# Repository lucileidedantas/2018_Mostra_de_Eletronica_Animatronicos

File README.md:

# 2018_Mostra_de_Eletronica_Animatronicos
Arquivos, esquemáticos, sketchs e algumas imagens e vídeos da Mostra de eletrônica de 2018 onde cada grupo desenvolveu um animal diferente. Todos os prototipos usaram como base a plataforma arduino.
Fotos e vídeos do evento podem ser vistas no link: https://photos.app.goo.gl/8ZrHkMYPwSaBPpQG6.
Alguns animais, feitos em mdf e cortados a laser, foram desenhados pelos proprios estudantes. Estes arquivos também estão nas pastas referentes ao projeto. 
Outros animais foram feito de material reciclavel e material de papelaria.

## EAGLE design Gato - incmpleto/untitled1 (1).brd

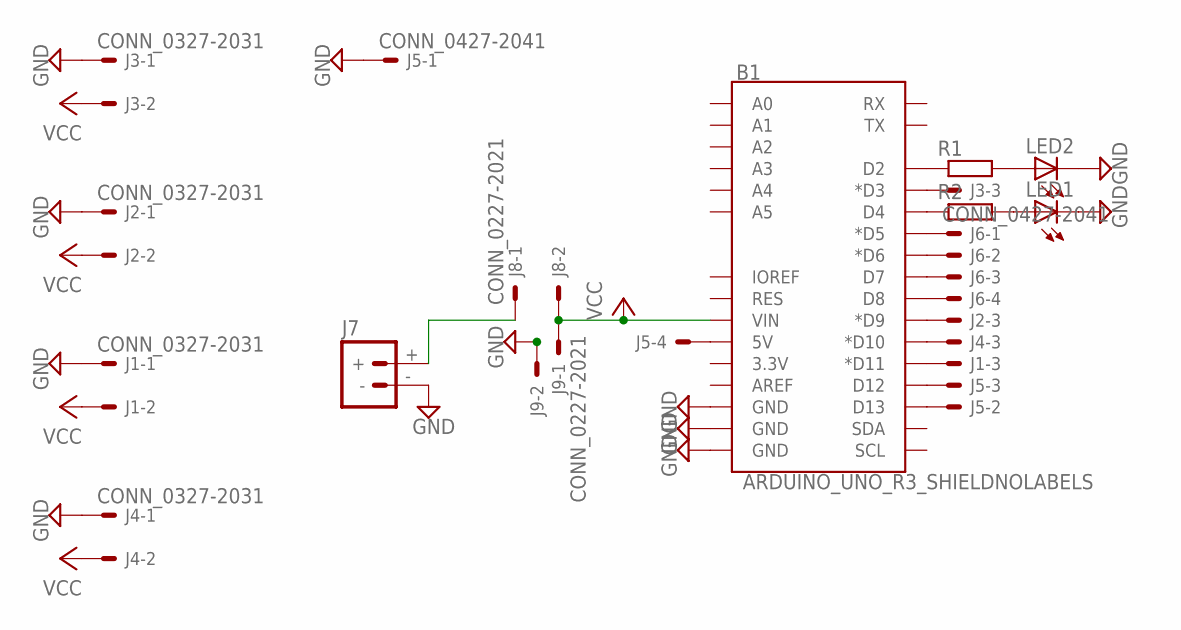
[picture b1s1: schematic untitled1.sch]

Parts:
B1: ARDUINO_UNO_R3_SHIELDNOLABELS; UNO_R3_SHIELD_NOLABELS
J1, J2, J3, J4: CONN_0327-2031; 6410-03
J5, J6: CONN_0427-2041; 6410-04
J7: BATTERY_CONNXT60; XT60
J8, J9: CONN_0227-2021; 6410-02
LED1, LED2: LED5MM
R1, R2: R-EU_0204/7; 0204/7

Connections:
GND: B1.GND@0 (GND), B1.GND@1 (GND), B1.GND@2 (GND), J1.1, J2.1, J3.1, J4.1, J5.1, J7.-, J9.2, LED1.K (C), LED2.K (C)
unnamed: B1.D3 (*D3), J3.3
unnamed: B1.D9 (*D9), J2.3
unnamed: B1.D11 (*D11), J1.3
unnamed: B1.D10 (*D10), J4.3
unnamed: B1.D13, J5.2
unnamed: B1.D12, J5.3
unnamed: B1.D5 (*D5), J6.1
unnamed: B1.D6 (*D6), J6.2
unnamed: B1.D7, J6.3
unnamed: B1.D8, J6.4
unnamed: B1.D2, R1.1
unnamed: B1.D4, R2.1
unnamed: LED2.A, R1.2
unnamed: LED1.A, R2.2
unnamed: J7.+, J8.1
unnamed: B1.5V, J5.4
VCC: B1.VIN, J1.2, J2.2, J3.2, J4.2, J8.2, J9.1

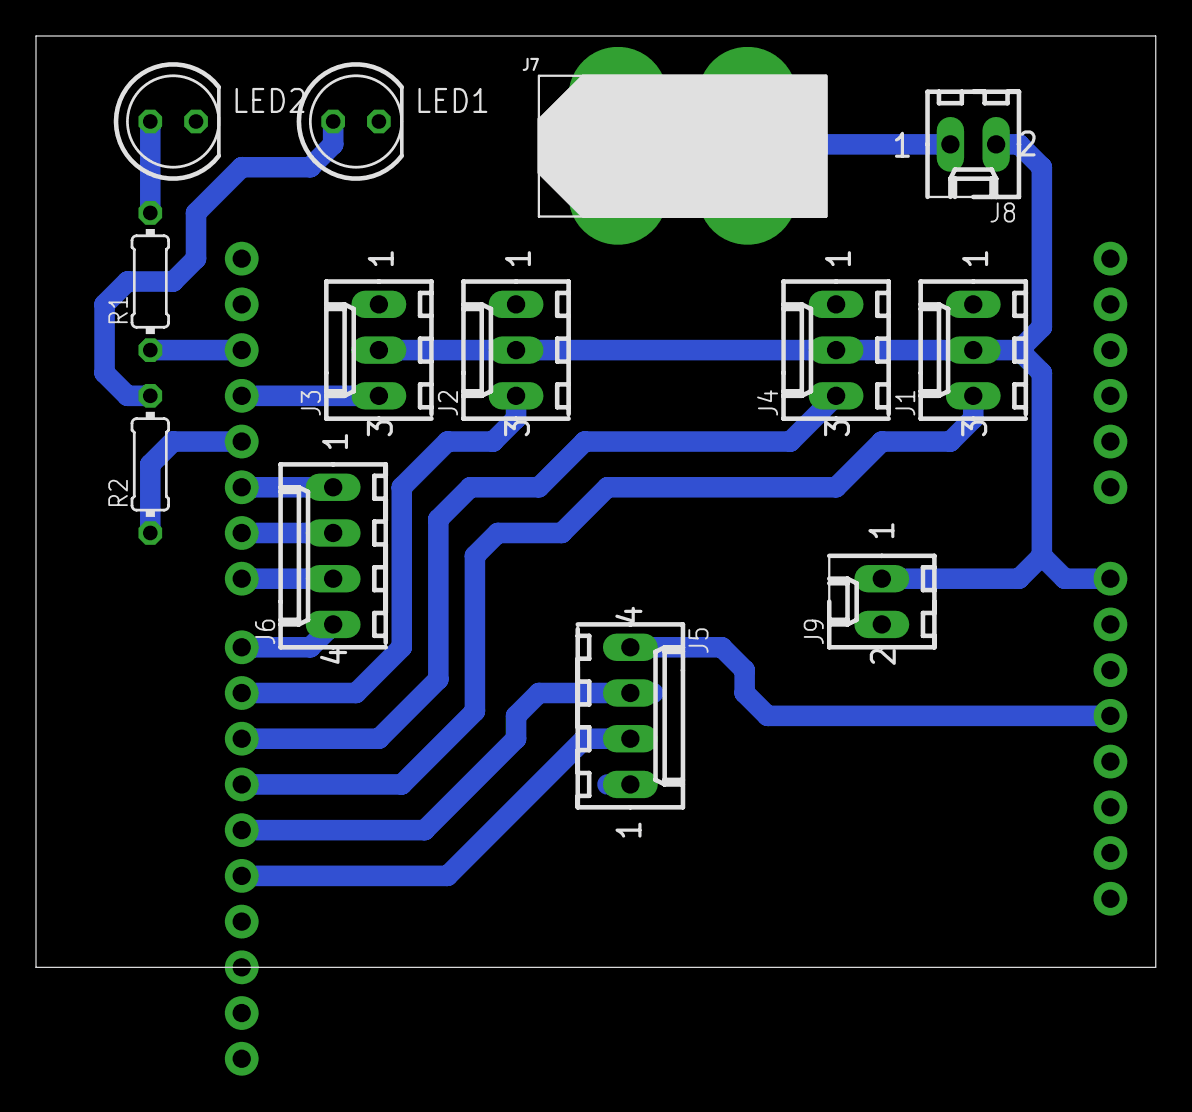
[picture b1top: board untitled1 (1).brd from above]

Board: 2 copper layers, 62.2 x 51.7 mm, 14 parts (0 on the bottom side), 18 nets.

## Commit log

2019-01-31 Arquivos enviados pelos alunos dos projetos
